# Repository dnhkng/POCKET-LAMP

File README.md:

# POCKET-LAMP
PCR-LAMP Diagnostic Device

This is my entry for the The COVID-19 Detect & Protect Challenge

Here you will find the code, schematics and 3D model you need to build a COVID19 virus detector.

Read a full description at [Hackster.io](https://www.hackster.io/dnhkng/the-pocket-lamp-illuminating-sars-cov-2-3a1d17).

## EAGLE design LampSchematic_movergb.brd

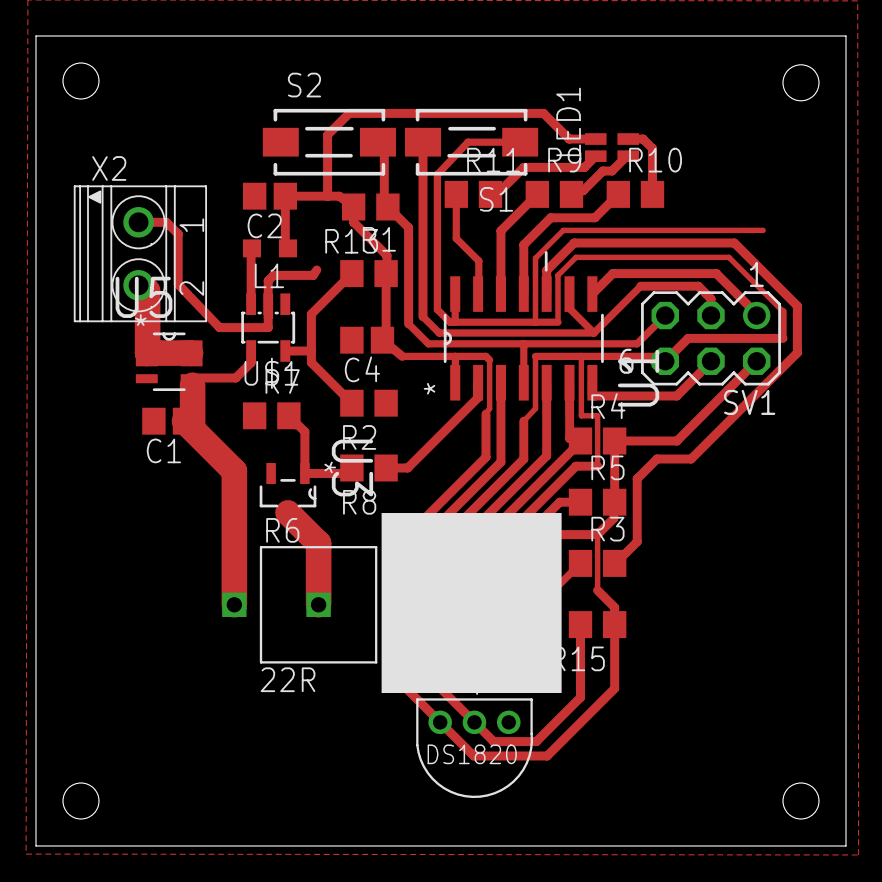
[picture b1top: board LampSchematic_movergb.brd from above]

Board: 2 copper layers, 45.0 x 45.0 mm, 29 parts (0 on the bottom side), 24 nets.

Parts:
C1, C4: 0.1uF; C0805
C2: 10uF; C0805
L1: 10uH; L2012C
LED1: GM1WA55311A
R1: 61.9k; R0805
R2: 20k; R0805
R3, R15: 6.8R; R0805
R4, R5: 4.7k; R0805
R6: 22R; 5WRESISTOR
R7: 100k; R0805
R8: 47R; R0805
R9: 330R; R0805
R10, R11: 68R; R0805
R13: 10k; R0805
S1, S2: DTSM-3
SV1: ISP; MA03-2
U1: ATTINY84-20SSU; SOIC127P600X175-14N
U2: VEML6040
U3: PMV20ENR; SOT95P230X110-3N
U5: Si3417DV; SOP95P285X110-6N
U$1: TPS560200; SOT23-5L
U$2: DS1820TO92; DS1820
U$3: UV; GM5BW96385A
X2: 1751248

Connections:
+12V: C1.1, R6.P$2, U5.4, U$1.4
BLUE: R11.1, U1.13
GND: C1.2, C2.2, C4.2, R2.1, R7.1, S1.1, S2.1, SV1.6, U1.14, U2.1, U3.2, U5.3, U$1.2, U$2.GND, U$3.2, X2.1
GREEN: R10.1, U1.11
HEAT: R8.1, U1.2
MISO: SV1.1, U1.8
MOSI: SV1.4, U1.7
unnamed: L1.2, U$1.3
unnamed: R1.1, R2.2, U$1.5
unnamed: R6.P$1, U3.3
unnamed: R7.2, R8.2, U3.1
unnamed: LED1.2, R9.2
unnamed: LED1.3, R10.2
unnamed: LED1.1, R11.2
unnamed: R3.1, U$3.1
unnamed: U5.1, U5.2, U5.5, U5.6, X2.2
RED: R9.1, U1.12
RES: R13.1, S2.2, SV1.5, U1.4
SCK: S1.2, SV1.3, U1.9
SCLK: R5.1, U1.5, U2.3
SDAT: R4.1, U1.6, U2.2
TEMP: R15.2, U1.3, U$2.DQ
UV: R3.2, U1.10
VCC: C2.1, C4.1, L1.1, LED1.4, R1.2, R4.2, R5.2, R13.2, R15.1, SV1.2, U1.1, U2.4, U$2.VDD

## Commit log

2015-09-03 Started a new Project on Github
2020-07-14 Datasheets for Components
2020-07-15 [feat] updated 3d model
2020-07-15 [feat] added images
2020-07-15 [fix] resized wire gap
2020-07-15 [feat] added picture of circuit
2020-07-15 [feat] Fluorospectrometer
2020-07-15 [feat] More Arduino testing code
2020-07-15 [feat] temp controller
2020-07-15 [feat] PID control test
2020-07-16 [fix] renamed for clarity
2020-07-16 Enlarged cable slot
